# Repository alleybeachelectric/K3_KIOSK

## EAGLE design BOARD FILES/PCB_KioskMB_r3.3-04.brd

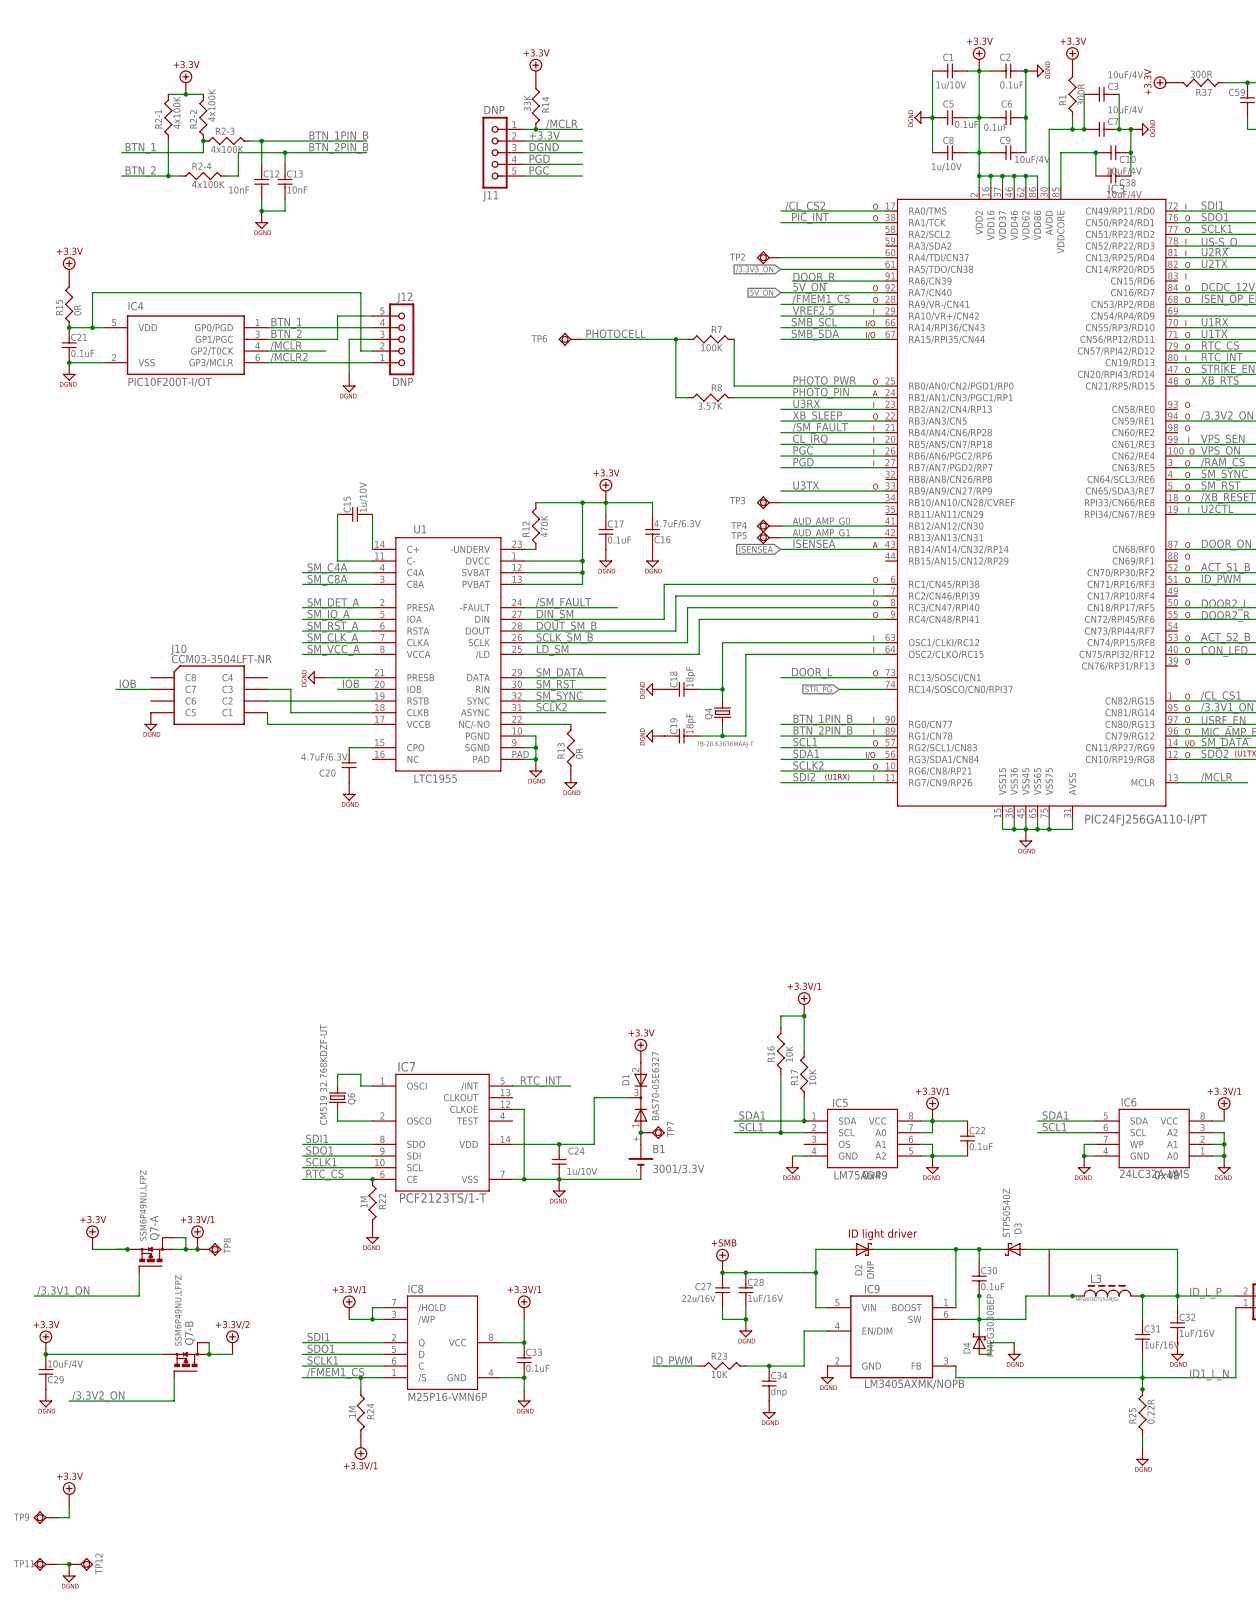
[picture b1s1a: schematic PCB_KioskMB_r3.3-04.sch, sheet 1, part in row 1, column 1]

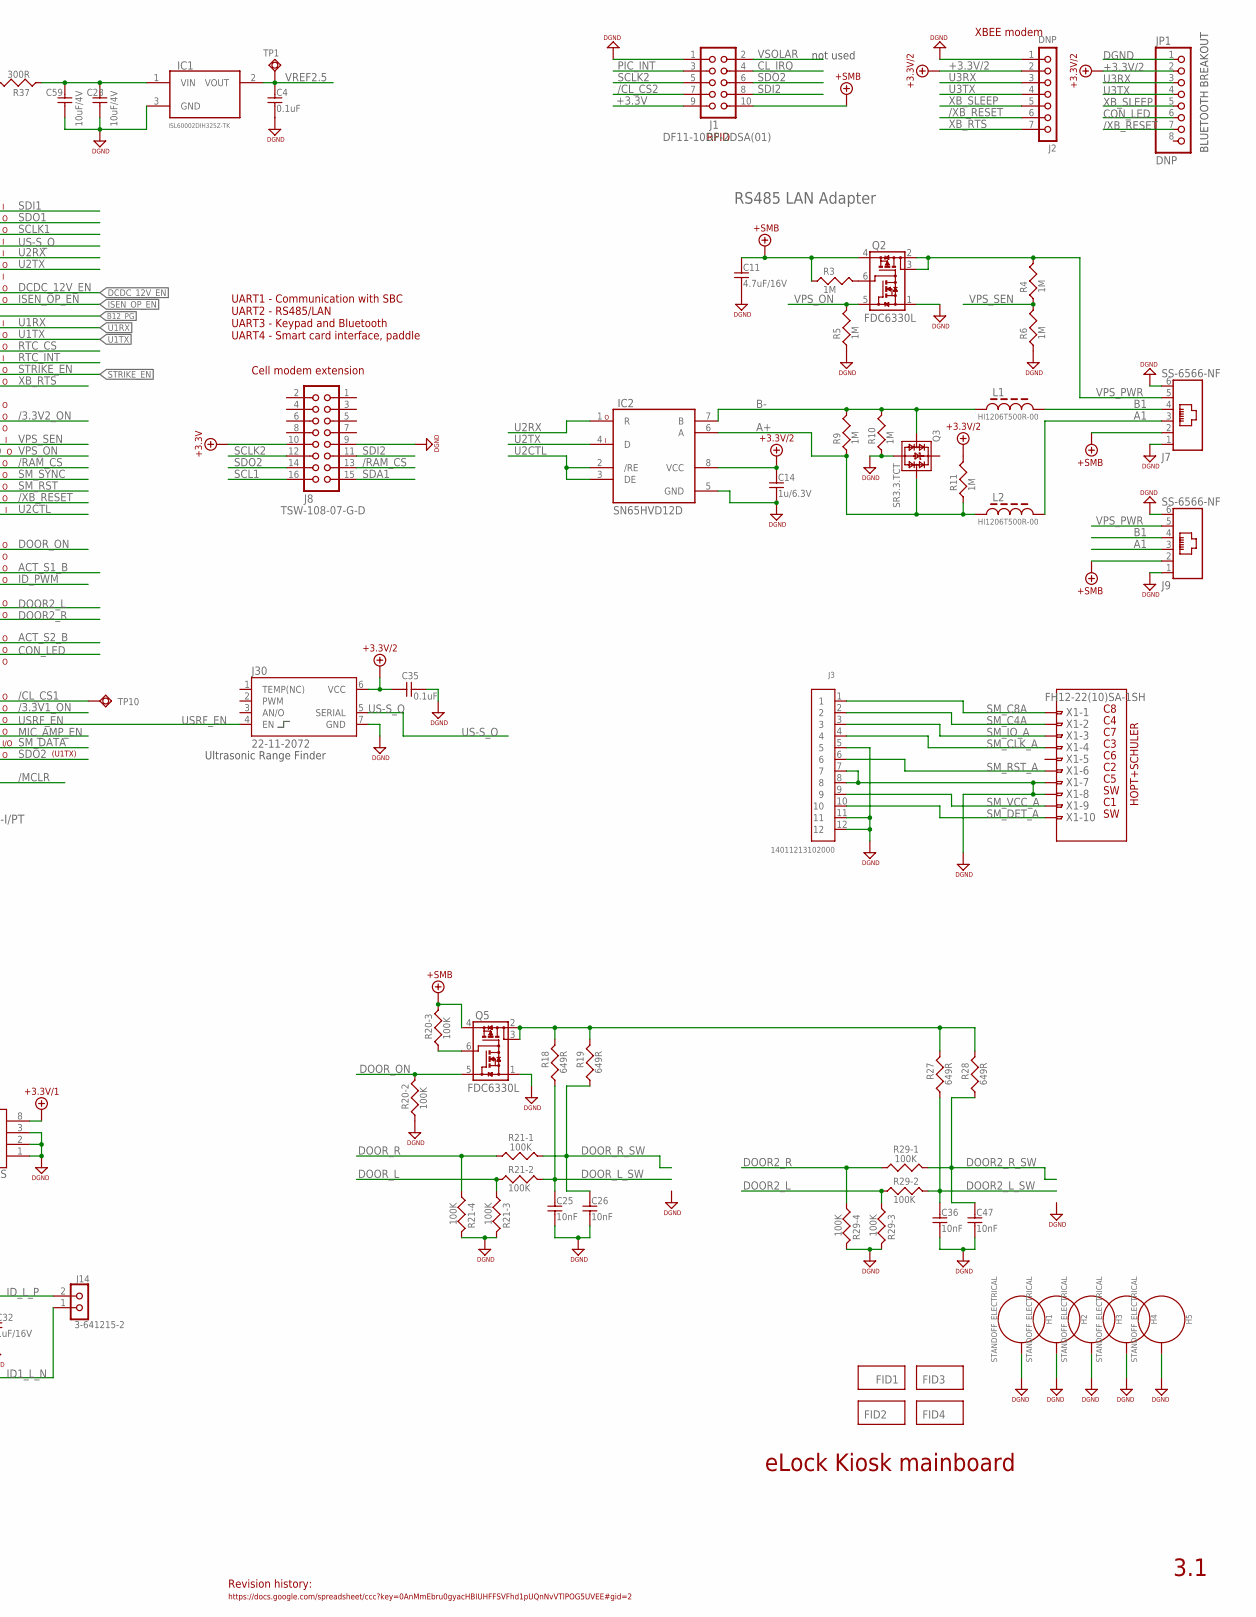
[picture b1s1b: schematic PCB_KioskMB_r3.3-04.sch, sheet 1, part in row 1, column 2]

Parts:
B1: 3001/3.3V; 3001
C1, C8, C15, C24: 1u/10V; 0603
C2, C4, C5, C6, C17, C21, C22, C30, C33, C35: 0.1uF; 0603
C3, C7, C9, C10, C23, C29, C38, C59: 10uF/4V; 0603
C11: 4.7uF/16V; 0805
C12, C13, C25, C26, C36, C47: 10nF; 0603
C14: 1u/6.3V; 0603
C16, C20: 4.7uF/6.3V; 0603
C18, C19: 18pF; 0603
C27: 22u/16V; 1210
C28, C31, C32: 1uF/16V; 0603
C34: dnp; 0603
D1: BAS70-05E6327; SOT-23
D2: DNP; SOD-123
D3: STPS0540Z; SOD-123
D4: PMEG3030BEP; SOD-128
FID1, FID2, FID3, FID4: REF
H1, H2, H3, H4, H5: STANDOFF_ELECTRICAL; STANDOFF-ELECTRICAL
IC1: ISL60002DIH325Z-TK; SOT-23
IC2: SN65HVD12D; SO08
IC3: PIC24FJ256GA110-I/PT; SQFP-S-12X12-100
IC4: PIC10F200T-I/OT; SOT23-6
IC5: LM75ADP; TSSOP08-3
IC6: 24LC32A-I/MS; MSOP-08
IC7: PCF2123TS/1-T; TSSOP014
IC8: M25P16-VMN6P; SO-08
IC9: LM3405AXMK/NOPB; SOT23-6
J1: DF11-10DP-2DSA(01); DF11-10DP-2DSA
J2: DNP; MA07-1
J3: 14011213102000
J7, J9: SS-6566-NF
J8: TSW-108-07-G-D; MA08-2
J10: CCM03-3504LFT-NR
J11, J12: DNP; MA05-1
J14: 3-641215-2
J30: 22-11-2072; HRXL-MAXSONAR-WRC-MB7387
JP1: DNP; 1X08-LOCK
L1, L2: HI1206T500R-00; 1206
L3: NRS8030T150MJGJ; NRS8030
Q2, Q5: FDC6330L; SSOT-6
Q3: SR3.3.TCT; SOT-143
Q4: 7B-28.63636MAAJ-T; 7B
Q6: CM519 32.768KDZF-UT; CM519
Q7: SSM6P49NU,LFPZ; MICRO_FET
R1, R37: 300R; 0603
R2: 4x100K; 0603-ARRAY
R3, R4, R5, R6, R9, R10, R11, R22, R24: 1M; 0603
R7: 100K; 0603
R8: 3.57K; 0603
R12: 470K; 0603-0RTOP
R13, R15: 0R; 0603-0RTOP
R14: 33K; 0603
R16, R17, R23: 10K; 0603-0RTOP
R18, R19, R27, R28: 649R; 0603
R20, R21, R29: 100K; 0603-ARRAY
R25: 0.22R; 0603-0RTOP
TP1, TP2, TP3, TP4, TP5, TP6, TP7, TP8, TP10: ROUND_SMD1MM; SMD_ROUND_1MM
TP9, TP11: ROUND_SMD0.7MM; SMD_ROUND_07MM
TP12: TP_0812; TP_0.8_1.2
U1: LTC1955; LFCSP_5X5_032
X1: FH12-22(10)SA-1SH; CON-FPC-1.0MM-10POS

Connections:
5V_ON: IC3.92 (RA7/CN40); also elsewhere on the board
+3.3V: C1.1, C2.1, C5.1, C6.1, C8.1, C9.1, C16.2, C17.1, C29.2, D1.2 (A2), IC3.2 (VDD2), IC3.16 (VDD16), IC3.37 (VDD37), IC3.46 (VDD46), IC3.62 (VDD62), IC3.86 (VDD86), J1.9, J8.10, J11.2, Q7.1 (S), Q7.4 (S), R1.2, R2.7 (2), R2.8 (2), R12.2, R14.2, R15.2, R37.2, TP9.P$1, U1.1 (DVCC), U1.12 (SVBAT), U1.13 (PVBAT); also elsewhere on the board
+3.3V/1: C22.1, C33.1, IC5.7 (A0), IC5.8 (VCC), IC6.8 (VCC), IC8.3 (/WP), IC8.7 (/HOLD), IC8.8 (VCC), Q7.6 (D), Q7.P1 (D1), R16.2, R17.2, R24.1, TP8.P$1; also elsewhere on the board
+3.3V/2: C14.1, C35.2, IC2.8 (VCC), J2.2, J30.6 (VCC), JP1.2, Q7.3 (D), Q7.P2 (D1), R11.2; also elsewhere on the board
+SMB: C11.1, C27.1, C28.1, D2.A, IC9.5 (VIN), J1.10, J7.2, J9.2, Q2.4 (Q2S), Q5.4 (Q2S), R3.1, R20.6 (2); also elsewhere on the board
/3.3V1_ON: IC3.95 (CN81/RG14), Q7.2 (G)
/3.3V2_ON: IC3.94 (CN59/RE1), Q7.5 (G)
/3.3V3_ON: IC3.61 (RA5/TDO/CN38)
/CL_CS1: IC3.1 (CN82/RG15), TP10.P$1
/CL_CS2: IC3.17 (RA0/TMS), J1.7
/FMEM1_CS: IC3.28 (RA9/VR-/CN41), IC8.1 (/S), R24.2
/MCLR: IC3.13 (MCLR), IC4.4 (GP2/T0CK), J11.1, R14.1
/MCLR2: IC4.6 (GP3/MCLR), J12.1
/RAM_CS: IC3.3 (CN63/RE5), J8.13
/SM_FAULT: IC3.21 (RB4/AN4/CN6/RP28), U1.24 (-FAULT)
/XB_RESET: IC3.18 (RPI33/CN66/RE8), J2.6, JP1.7
A1: J7.3, J9.3, L2.2
A+: IC2.6 (A), L2.1, Q3.3, R9.1, R11.1
ACT_S1_B: IC3.52 (CN70/RP30/RF2); also elsewhere on the board
ACT_S2_B: IC3.53 (CN74/RP15/RF8); also elsewhere on the board
AUD_AMP_G0: IC3.41 (RB12/AN12/CN30), TP4.P$1; also elsewhere on the board
AUD_AMP_G1: IC3.42 (RB13/AN13/CN31), TP5.P$1; also elsewhere on the board
B1: J7.4, J9.4, L1.2
B12_PG: IC3.69 (CN54/RP4/RD9); also elsewhere on the board
B-: IC2.7 (B), L1.1, Q3.2, R9.2, R10.2
BTN_1: IC4.1 (GP0/PGD), J12.4, R2.2 (1), R2.3 (1); also elsewhere on the board
BTN_1PIN_B: C12.1, IC3.90 (RG0/CN77), R2.6 (2)
BTN_2: IC4.3 (GP1/PGC), J12.5, R2.1, R2.4 (1); also elsewhere on the board
BTN_2PIN_B: C13.1, IC3.89 (RG1/CN78), R2.5 (2)
CL_IRQ: IC3.20 (RB5/AN5/CN7/RP18), J1.4
CON_LED: IC3.40 (CN75/RPI32/RF12), JP1.6
DCDC_12V_EN: IC3.84 (CN16/RD7); also elsewhere on the board
DGND: B1.-, C1.2, C2.2, C3.2, C4.2, C5.2, C6.2, C7.2, C8.2, C9.2, C10.1, C11.2, C12.2, C13.2, C14.2, C16.1, C17.2, C18.1, C19.1, C20.1, C21.2, C22.2, C23.2, C24.2, C25.2, C26.2, C27.2, C28.2, C29.1, C32.2, C33.2, C34.2, C35.1, C36.2, C38.1, C47.2, C59.2, D4.A, H1.P1, H2.P1, H3.P1, H4.P1, H5.P1, IC1.3 (GND), IC2.5 (GND), IC3.15 (VSS15), IC3.31 (AVSS), IC3.36 (VSS36), IC3.45 (VSS45), IC3.65 (VSS65), IC3.75 (VSS75), IC4.2 (VSS), IC5.4 (GND), IC5.5 (A2), IC5.6 (A1), IC6.1 (A0), IC6.2 (A1), IC6.3 (A2), IC6.4 (GND), IC6.7 (WP), IC7.7 (VSS), IC7.12 (CLKOE), IC8.4 (GND), IC9.2 (GND), J1.1, J2.1, J3.5, J3.7, J3.8, J3.11, J3.12, J7.1, J7.6, J8.9, J9.1, J9.6, J10.C5, J11.3, J12.3, J30.7 (GND), JP1.1, Q2.1 (Q1S), Q3.1, Q5.1 (Q1S), R5.1, R6.1, R10.1, R13.1, R20.2 (1), R21.5 (2), R21.6 (2), R22.1, R25.1, R29.5 (2), R29.6 (2), TP11.P$1, TP12.1, U1.9 (SGND), U1.10 (PGND), U1.21 (PRESB), U1.PAD, X1.7, X1.8; also elsewhere on the board
DIN_SM: IC3.6 (RC1/CN45/RPI38), U1.27 (DIN)
DOOR2_L: IC3.50 (CN18/RP17/RF5), R29.2 (1), R29.3 (1)
DOOR2_L_SW: C36.1, R27.2, R29.7 (2); also elsewhere on the board
DOOR2_R: IC3.55 (CN72/RPI45/RF6), R29.1, R29.4 (1)
DOOR2_R_SW: C47.1, R28.2, R29.8 (2); also elsewhere on the board
DOOR_L: IC3.73 (RC13/SOSCI/CN1), R21.2 (1), R21.3 (1)
DOOR_L_SW: C25.1, R18.2, R21.7 (2); also elsewhere on the board
DOOR_ON: IC3.87 (CN68/RF0), Q5.5 (Q1G), R20.7 (2)
DOOR_R: IC3.91 (RA6/CN39), R21.1, R21.4 (1)
DOOR_R_SW: C26.1, R19.2, R21.8 (2); also elsewhere on the board
DOUT_SM_B: IC3.7 (RC2/CN46/RPI39), U1.28 (DOUT)
ID1_L_N: C31.2, IC9.3 (FB), J14.1, R25.2; also elsewhere on the board
ID_L_P: C31.1, C32.1, D3.A, J14.2, L3.2; also elsewhere on the board
ID_PWM: IC3.51 (CN71/RP16/RF3), R23.1
IOB: J10.C7, U1.20 (IOB)
ISENSEA: IC3.43 (RB14/AN14/CN32/RP14); also elsewhere on the board
ISEN_OP_EN: IC3.68 (CN53/RP2/RD8); also elsewhere on the board
LD_SM: IC3.9 (RC4/CN48/RPI41), U1.25 (/LD)
MIC_AMP_EN: IC3.96 (CN79/RG12); also elsewhere on the board
unnamed: C10.2, C38.2, IC3.85 (VDDCORE)
unnamed: C20.2, U1.15 (CPO)
unnamed: B1.+, D1.1 (A1), TP7.P$1
unnamed: J10.C2, U1.19 (RSTB)
unnamed: C19.2, IC3.64 (OSC2/CLKO/RC15), Q4.1
unnamed: C15.1, U1.11 (C-)
unnamed: C15.2, U1.14 (C+)
unnamed: C24.1, D1.3 (K), IC7.14 (VDD)
unnamed: R12.1, U1.23 (-UNDERV)
unnamed: IC7.1 (OSCI), Q6.2
unnamed: IC7.2 (OSCO), Q6.1
unnamed: R13.2, U1.22 (NC/-NO)
unnamed: J10.C3, U1.18 (CLKB)
unnamed: J10.C1, U1.17 (VCCB)
unnamed: Q5.6 (Q2G), R20.3 (1)
unnamed: C18.2, IC3.63 (OSC1/CLKI/RC12), Q4.3 (2)
unnamed: C23.1, C59.1, IC1.1 (VIN), R37.1
unnamed: Q5.2 (Q2D1), Q5.3 (Q2D2), R18.1, R19.1, R27.1, R28.1
unnamed: C21.1, IC4.5 (VDD), J12.2, R15.1
unnamed: IC3.34 (RB10/AN10/CN28/CVREF), TP3.P$1
unnamed: C3.1, C7.1, IC3.30 (AVDD), R1.1
unnamed: IC3.60 (RA4/TDI/CN37), TP2.P$1
unnamed: C34.1, IC9.4 (EN/DIM), R23.2
unnamed: C30.2, D4.K, IC9.6 (SW), L3.1
unnamed: C30.1, D2.C (K), D3.C (K), IC9.1 (BOOST)
unnamed: Q2.6 (Q2G), R3.2
PGC: IC3.26 (RB6/AN6/PGC2/RP6), J11.5
PGD: IC3.27 (RB7/AN7/PGD2/RP7), J11.4
PHOTOCELL: R7.2, R8.2, TP6.P$1
PHOTO_PIN: IC3.24 (RB1/AN1/CN3/PGC1/RP1), R8.1
PHOTO_PWR: IC3.25 (RB0/AN0/CN2/PGD1/RP0), R7.1
PIC_INT: IC3.38 (RA1/TCK), J1.3
RTC_CS: IC3.79 (CN57/RPI42/RD12), IC7.6 (CE), R22.2
RTC_INT: IC3.80 (CN19/RD13), IC7.5 (/INT)
SCL1: IC3.57 (RG2/SCL1/CN83), IC5.2 (SCL), IC6.6 (SCL), J8.16, R16.1; also elsewhere on the board
SCLK1: IC3.77 (CN51/RP23/RD2), IC7.10 (SCL), IC8.6 (C)
SCLK2: IC3.10 (RG6/CN8/RP21), J1.5, J8.12, U1.31 (ASYNC)
SCLK_SM_B: IC3.8 (RC3/CN47/RPI40), U1.26 (SCLK)
SDA1: IC3.56 (RG3/SDA1/CN84), IC5.1 (SDA), IC6.5 (SDA), J8.15, R17.1; also elsewhere on the board
SDI1: IC3.72 (CN49/RP11/RD0), IC7.8 (SDO), IC8.2 (Q)
SDI2: IC3.11 (RG7/CN9/RP26), J1.8, J8.11
SDO1: IC3.76 (CN50/RP24/RD1), IC7.9 (SDI), IC8.5 (D)
SDO2: IC3.12 (CN10/RP19/RG8), J1.6, J8.14
SMB_SCL: IC3.66 (RA14/RPI36/CN43); also elsewhere on the board
SMB_SDA: IC3.67 (RA15/RPI35/CN44); also elsewhere on the board
SM_C4A: J3.2, U1.4 (C4A), X1.2
SM_C8A: J3.1, U1.3 (C8A), X1.1
SM_CLK_A: J3.4, U1.7 (CLKA), X1.4
SM_DATA: IC3.14 (CN11/RP27/RG9), U1.29 (DATA)
SM_DET_A: J3.10, U1.2 (PRESA), X1.10
SM_IO_A: J3.3, U1.5 (IOA), X1.3
SM_RST: IC3.5 (CN65/SDA3/RE7), U1.30 (RIN)
SM_RST_A: J3.6, U1.6 (RSTA), X1.6
SM_SYNC: IC3.4 (CN64/SCL3/RE6), U1.32 (SYNC)
SM_VCC_A: J3.9, U1.8 (VCCA), X1.9
STRIKE_EN: IC3.47 (CN20/RPI43/RD14); also elsewhere on the board
STR_PG: IC3.74 (RC14/SOSCO/CN0/RPI37); also elsewhere on the board
U1RX: IC3.70 (CN55/RP3/RD10); also elsewhere on the board
U1TX: IC3.71 (CN56/RP12/RD11); also elsewhere on the board
U2CTL: IC2.2 (/RE), IC2.3 (DE), IC3.19 (RPI34/CN67/RE9)
U2RX: IC2.1 (R), IC3.81 (CN13/RP25/RD4)
U2TX: IC2.4 (D), IC3.82 (CN14/RP20/RD5)
U3RX: IC3.23 (RB2/AN2/CN4/RP13), J2.3, JP1.3
U3TX: IC3.33 (RB9/AN9/CN27/RP9), J2.4, JP1.4
US-S_O: IC3.78 (CN52/RP22/RD3), J30.5 (SERIAL); also elsewhere on the board
USRF_EN: IC3.97 (CN80/RG13), J30.4 (EN); also elsewhere on the board
VPS_ON: IC3.100 (CN62/RE4), Q2.5 (Q1G), R5.2
VPS_PWR: J7.5, J9.5, Q2.2 (Q2D1), Q2.3 (Q2D2), R4.2
VPS_SEN: IC3.99 (CN61/RE3), R4.1, R6.2
VREF2.5: C4.1, IC1.2 (VOUT), IC3.29 (RA10/VR+/CN42), TP1.P$1
VSOLAR: J1.2
XB_RTS: IC3.48 (CN21/RP5/RD15), J2.7
XB_SLEEP: IC3.22 (RB3/AN3/CN5), J2.5, JP1.5

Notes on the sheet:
Cell modem extension
XBEE modem
I/O
3.1
eLock Kiosk mainboard
(U1RX)
(U1TX)
Revision history:
https://docs.google.com/spreadsheet/ccc?key=0AnMmEbru0gyacHBIUHFFSVFhd1pUQnNvVTlPOG5UVEE#gid=2
ID light driver
UART1 - Communication with SBC UART2 - RS485/LAN UART3 - Keypad and Bluetooth UART4 - Smart card interface, paddle
RS485 LAN Adapter
Ultrasonic Range Finder
HOPT+SCHULER
0x49
0x48
RFID
BLUETOOTH BREAKOUT
not used

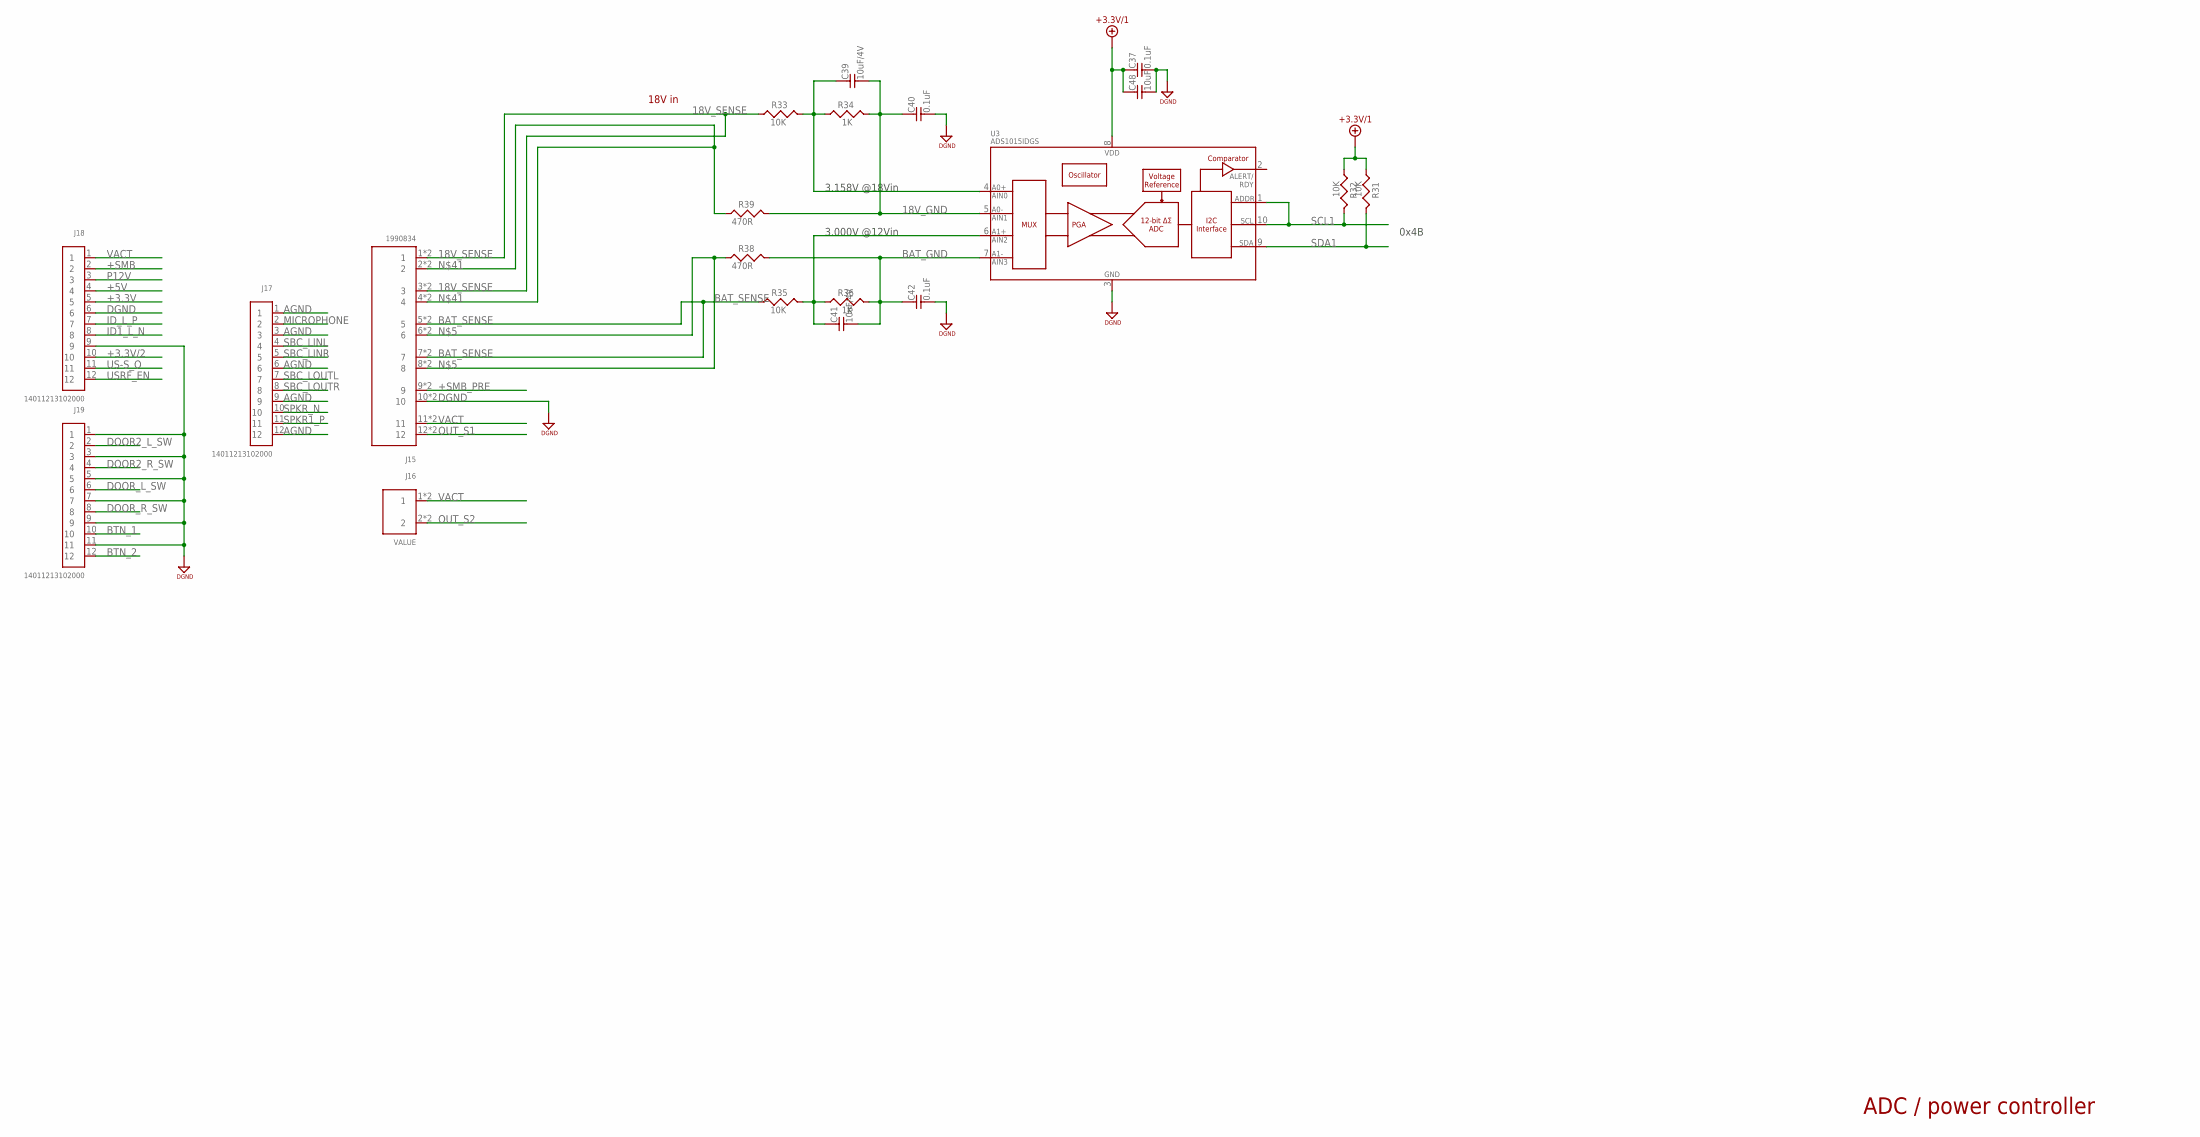
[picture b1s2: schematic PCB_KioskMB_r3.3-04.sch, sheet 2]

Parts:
C37, C40, C42: 0.1uF; 0603
C39, C41: 10uF/4V; 0603
C48: 10uF; 0603
J15: 1990834
J16: 1990737
J17, J18, J19: 14011213102000
R31, R32, R33, R35: 10K; 0603
R34, R36: 1K; 0603
R38, R39: 470R; 0603
U3: ADS1015IDGS; MSOP10

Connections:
18V_GND: C39.2, C40.1, R34.1, R39.1, U3.5 (AIN1)
18V_SENSE: J15.1, J15.1A (1), J15.3, J15.3A (3), R33.2
+3.3V: J18.5; also elsewhere on the board
+3.3V/1: C37.1, C48.1, R31.2, R32.2, U3.8 (VDD); also elsewhere on the board
+3.3V/2: J18.10; also elsewhere on the board
+5V: J18.4; also elsewhere on the board
+SMB: J18.2; also elsewhere on the board
+SMB_PRE: J15.9, J15.9A (9); also elsewhere on the board
AGND: J17.1, J17.3, J17.6, J17.9, J17.12; also elsewhere on the board
BAT_GND: C41.2, C42.1, R36.1, R38.1, U3.7 (AIN3)
BAT_SENSE: J15.5, J15.5A (5), J15.7, J15.7A (7), R35.2
BTN_1: J19.10; also elsewhere on the board
BTN_2: J19.12; also elsewhere on the board
DGND: C37.2, C40.2, C42.2, C48.2, J15.10, J15.10A (10), J18.6, J18.9, J19.1, J19.3, J19.5, J19.7, J19.9, J19.11, U3.3 (VSS); also elsewhere on the board
DOOR2_L_SW: J19.2; also elsewhere on the board
DOOR2_R_SW: J19.4; also elsewhere on the board
DOOR_L_SW: J19.6; also elsewhere on the board
DOOR_R_SW: J19.8; also elsewhere on the board
ID1_L_N: J18.8; also elsewhere on the board
ID_L_P: J18.7; also elsewhere on the board
MICROPHONE: J17.2; also elsewhere on the board
unnamed: J15.6, J15.6A (6), J15.8, J15.8A (8), R38.2
unnamed: C39.1, R33.1, R34.2, U3.4 (AIN0)
unnamed: C41.1, R35.1, R36.2, U3.6 (AIN2)
unnamed: J15.2, J15.2A (2), J15.4, J15.4A (4), R39.2
OUT_S1: J15.12, J15.12A (12); also elsewhere on the board
OUT_S2: J16.2, J16.2A (2); also elsewhere on the board
P12V: J18.3; also elsewhere on the board
SBC_LINL: J17.4; also elsewhere on the board
SBC_LINR: J17.5; also elsewhere on the board
SBC_LOUTL: J17.7; also elsewhere on the board
SBC_LOUTR: J17.8; also elsewhere on the board
SCL1: R32.1, U3.1 (ADDR), U3.10 (SCL); also elsewhere on the board
SDA1: R31.1, U3.9 (SDA); also elsewhere on the board
SPKR1_P: J17.11; also elsewhere on the board
SPKR_N: J17.10; also elsewhere on the board
US-S_O: J18.11; also elsewhere on the board
USRF_EN: J18.12; also elsewhere on the board
VACT: J15.11, J15.11A (11), J16.1, J16.1A (1), J18.1; also elsewhere on the board

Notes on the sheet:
ADC / power controller
0x4B
18V in
3.158V @18Vin
3.000V @12Vin

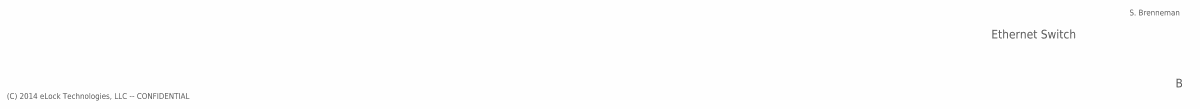
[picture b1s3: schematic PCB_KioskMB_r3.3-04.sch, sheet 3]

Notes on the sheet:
(C) 2014 eLock Technologies, LLC -- CONFIDENTIAL
S. Brenneman
Ethernet Switch

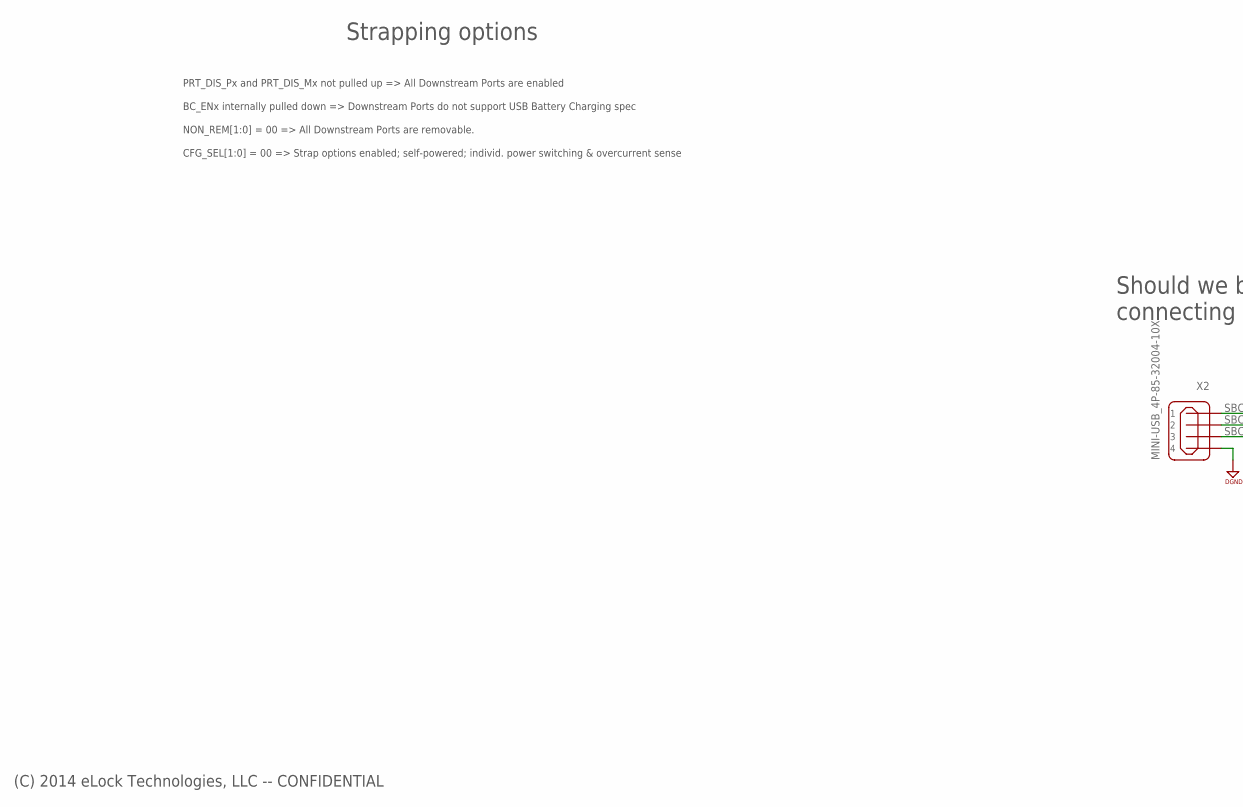
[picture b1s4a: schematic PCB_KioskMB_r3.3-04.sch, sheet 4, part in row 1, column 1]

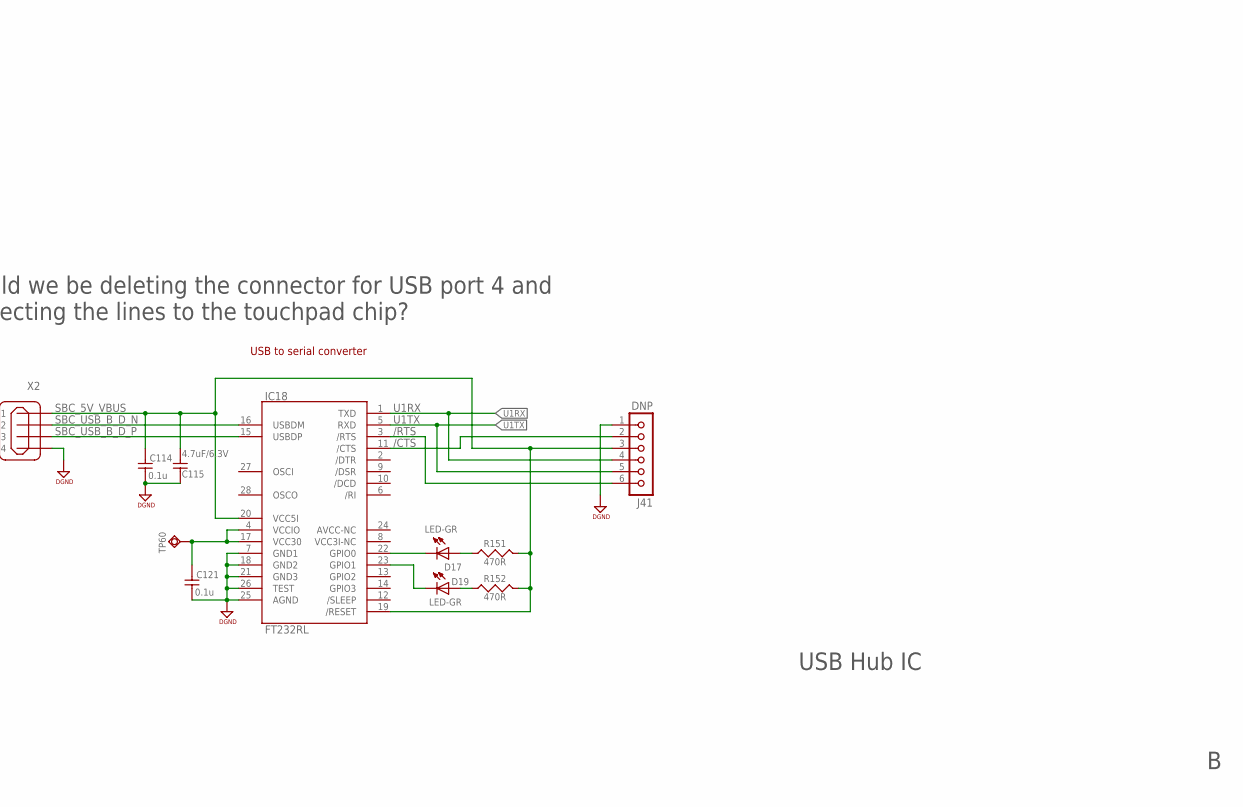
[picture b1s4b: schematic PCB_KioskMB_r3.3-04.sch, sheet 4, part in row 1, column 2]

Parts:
C114, C121: 0.1u; 0603
C115: 4.7uF/6.3V; 0603
D17, D19: LED-GR; 0805-POL
IC18: FT232RL; SSOP28DB
J41: DNP; MA06-1
R151, R152: 470R; 0603
TP60: ROUND_SMD0.7MM; SMD_ROUND_07MM
X2: MINI-USB_4P-85-32004-10X; 85-32004-10X

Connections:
/CTS: IC18.11 (/CTS), J41.2
/RTS: IC18.3 (/RTS), J41.6
DGND: C114.1, C115.1, C121.1, IC18.7 (GND1), IC18.18 (GND2), IC18.21 (GND3), IC18.25 (AGND), IC18.26 (TEST), J41.1, X2.4; also elsewhere on the board
unnamed: C121.2, IC18.4 (VCCIO), IC18.17 (VCC30), TP60.P$1
unnamed: D17.1+ (K), IC18.22 (GPIO0)
unnamed: D19.1+ (K), IC18.23 (GPIO1)
unnamed: D17.2 (A), R151.1
unnamed: D19.2 (A), R152.1
SBC_5V_VBUS: C114.2, C115.2, IC18.19 (/RESET), IC18.20 (VCC5I), J41.3, R151.2, R152.2, X2.1
SBC_USB_B_D_N: IC18.16 (USBDM), X2.2
SBC_USB_B_D_P: IC18.15 (USBDP), X2.3
U1RX: IC18.1 (TXD), J41.4; also elsewhere on the board
U1TX: IC18.5 (RXD), J41.5; also elsewhere on the board

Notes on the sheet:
(C) 2014 eLock Technologies, LLC -- CONFIDENTIAL
USB Hub IC
PRT_DIS_Px and PRT_DIS_Mx not pulled up => All Downstream Ports are enabled
Strapping options
BC_ENx internally pulled down => Downstream Ports do not support USB Battery Charging spec
NON_REM[1:0] = 00 => All Downstream Ports are removable.
CFG_SEL[1:0] = 00 => Strap options enabled; self-powered; individ. power switching & overcurrent sense
Should we be deleting the connector for USB port 4 and connecting the lines to the touchpad chip?
USB to serial converter

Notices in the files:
parts and their libraries:
SparkFun-Hardware: Licensing: Creative Commons ShareAlike 4.0 International - https://creativecommons.org/licenses/by-sa/4.0
